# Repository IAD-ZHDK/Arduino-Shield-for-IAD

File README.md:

# Arduino-Shield-for-IAD

A simple prototyping shield with Lynx Smart Servo and qwiic/stema connectors for both Ardiuino UNO and MKR board shapes.  

MKR                                                      |  UNO 
:-------------------------------------------------------:|:--------------------------------------------------------:
 |   

The arduino UNO shield uses the following pins for software serial to the LYNX smart servo connector:

rxPin 8

txPin 9

The MKR shield uses the following pins for hardware serial (SAMD21 devices) the LYNX smart servo connector: 

rxPin 1

txPin 0

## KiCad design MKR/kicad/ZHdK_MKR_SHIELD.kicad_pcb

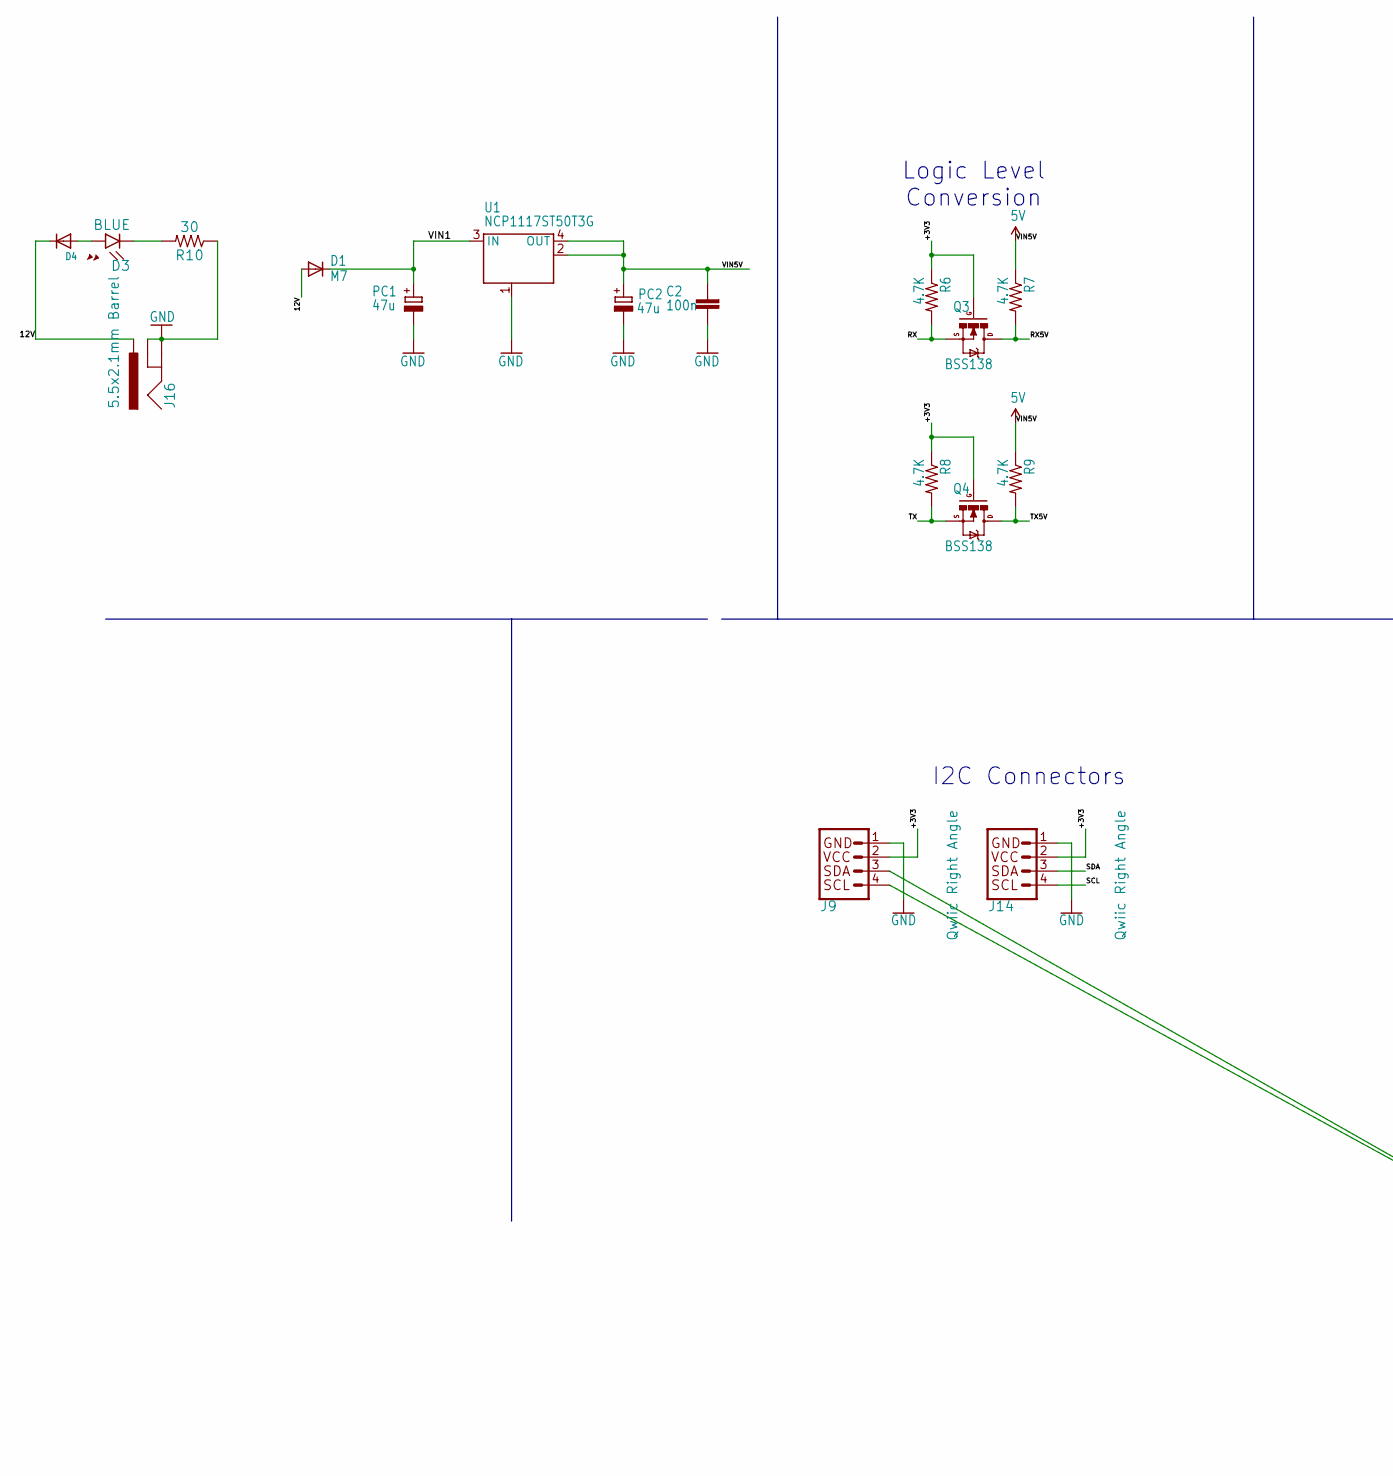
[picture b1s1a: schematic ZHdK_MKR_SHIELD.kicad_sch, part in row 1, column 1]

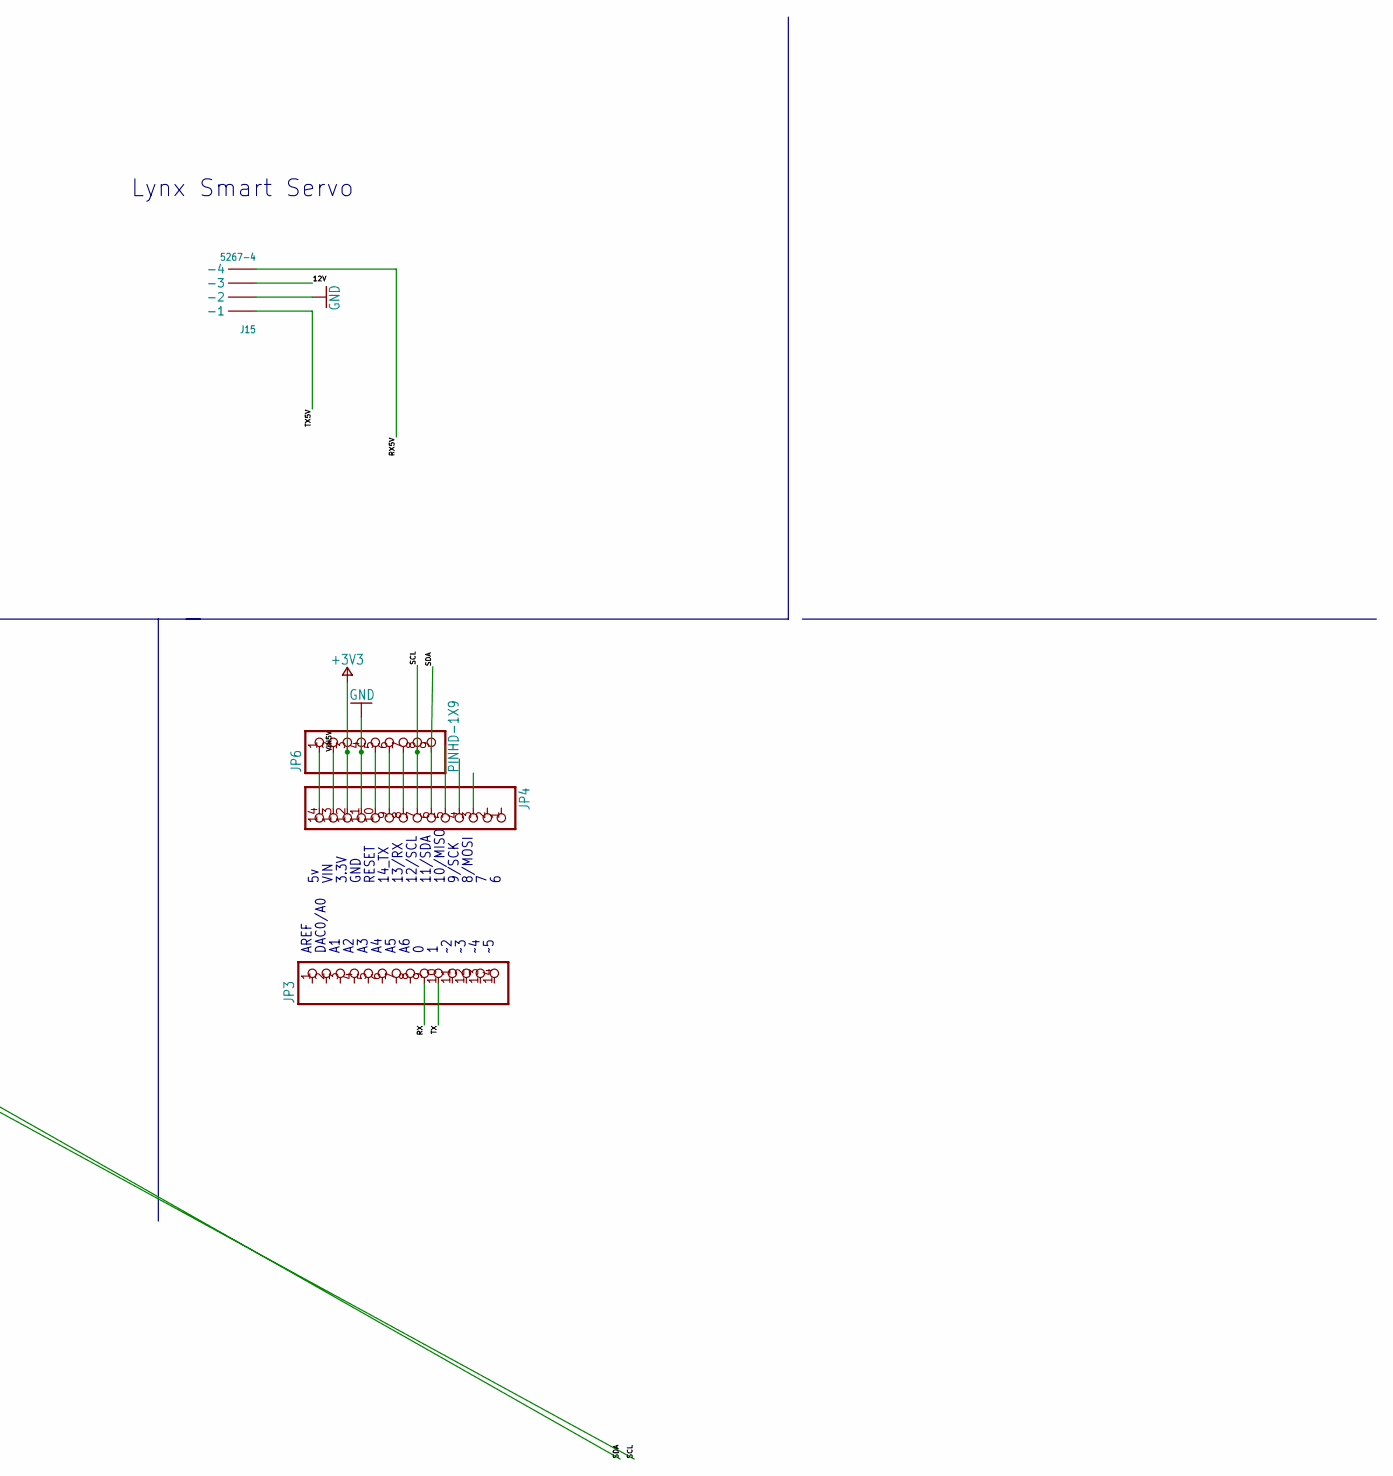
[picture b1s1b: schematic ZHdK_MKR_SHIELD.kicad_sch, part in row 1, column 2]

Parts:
C2: 100n; C0603-ROUND
D1: M7; SMB
D3: BLUE; LED-0603
D4: 9V; SOD-123
J9, J14: Qwiic Right Angle; 1X04_1MM_RA
J15: 5267-4
J16: 5.5x2.1mm Barrel; POWER_JACK_SMD
JP3, JP4: -; 1X14
JP6: PINHD-1X9; 1X09
PC1, PC2: 47u; PANASONIC_D
Q3, Q4: BSS138; SOT23-3
R6, R7, R8, R9: 4.7K; 0603-RES
R10: 30; 0603
U1: NCP1117ST50T3G; SOT223

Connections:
12V: D1.A, D4.C, J15.P$3 (-3), J16.VIN0 (PWR)
+3V3: J9.2, J14.2, JP4.12, JP6.3, Q3.1 (G), Q4.1 (G), R6.1, R8.1
GND: C2.1, J9.1, J14.1, J15.P$2 (-2), J16.GND (GNDBREAK), J16.P$4 (GND), JP4.11, JP6.4, PC1.-, PC2.-, R10.1, U1.1 (GND/ADJ)
unnamed: JP4.14, JP6.1
unnamed: JP4.10, JP6.5
unnamed: JP4.9, JP6.6
unnamed: JP4.8, JP6.7
unnamed: D3.A, D4.A
unnamed: D3.C, R10.2
RX: JP3.9, Q3.2 (S), R6.2
RX5V: J15.P$4 (-4), Q3.3 (D), R7.2
SCL: J9.4, J14.4, JP4.7, JP6.8
SDA: J9.3, J14.3, JP4.6, JP6.9
TX: JP3.10, Q4.2 (S), R8.2
TX5V: J15.P$1 (-1), Q4.3 (D), R9.2
VIN1: D1.C, PC1.+, U1.3 (IN)
VIN5V: C2.2, JP4.13, JP6.2, PC2.+, R7.1, R9.1, U1.2 (OUT@1), U1.4 (OUT)

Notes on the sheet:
GND
3.3V
I2C Connectors
8/MOSI
AREF
11/SDA
9/SCK
13/RX
10/MISO
RESET
Lynx Smart Servo
14_TX
DAC0/A0
12/SCL
Logic Level Conversion
VIN

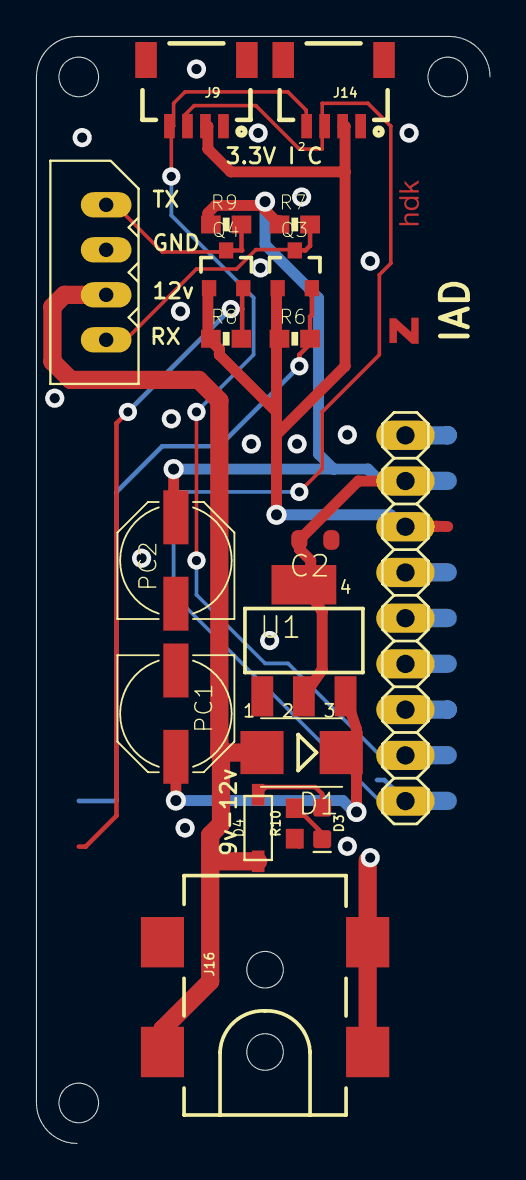
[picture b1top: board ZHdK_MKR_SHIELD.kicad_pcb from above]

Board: 2 copper layers, 25.2 x 61.5 mm, 23 parts (0 on the bottom side), 13 nets.

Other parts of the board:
U$2: ZHDK_LOGO
UNK_HOLE_0: dummyfp0
UNK_HOLE_2: dummyfp2
UNK_HOLE_3: dummyfp3

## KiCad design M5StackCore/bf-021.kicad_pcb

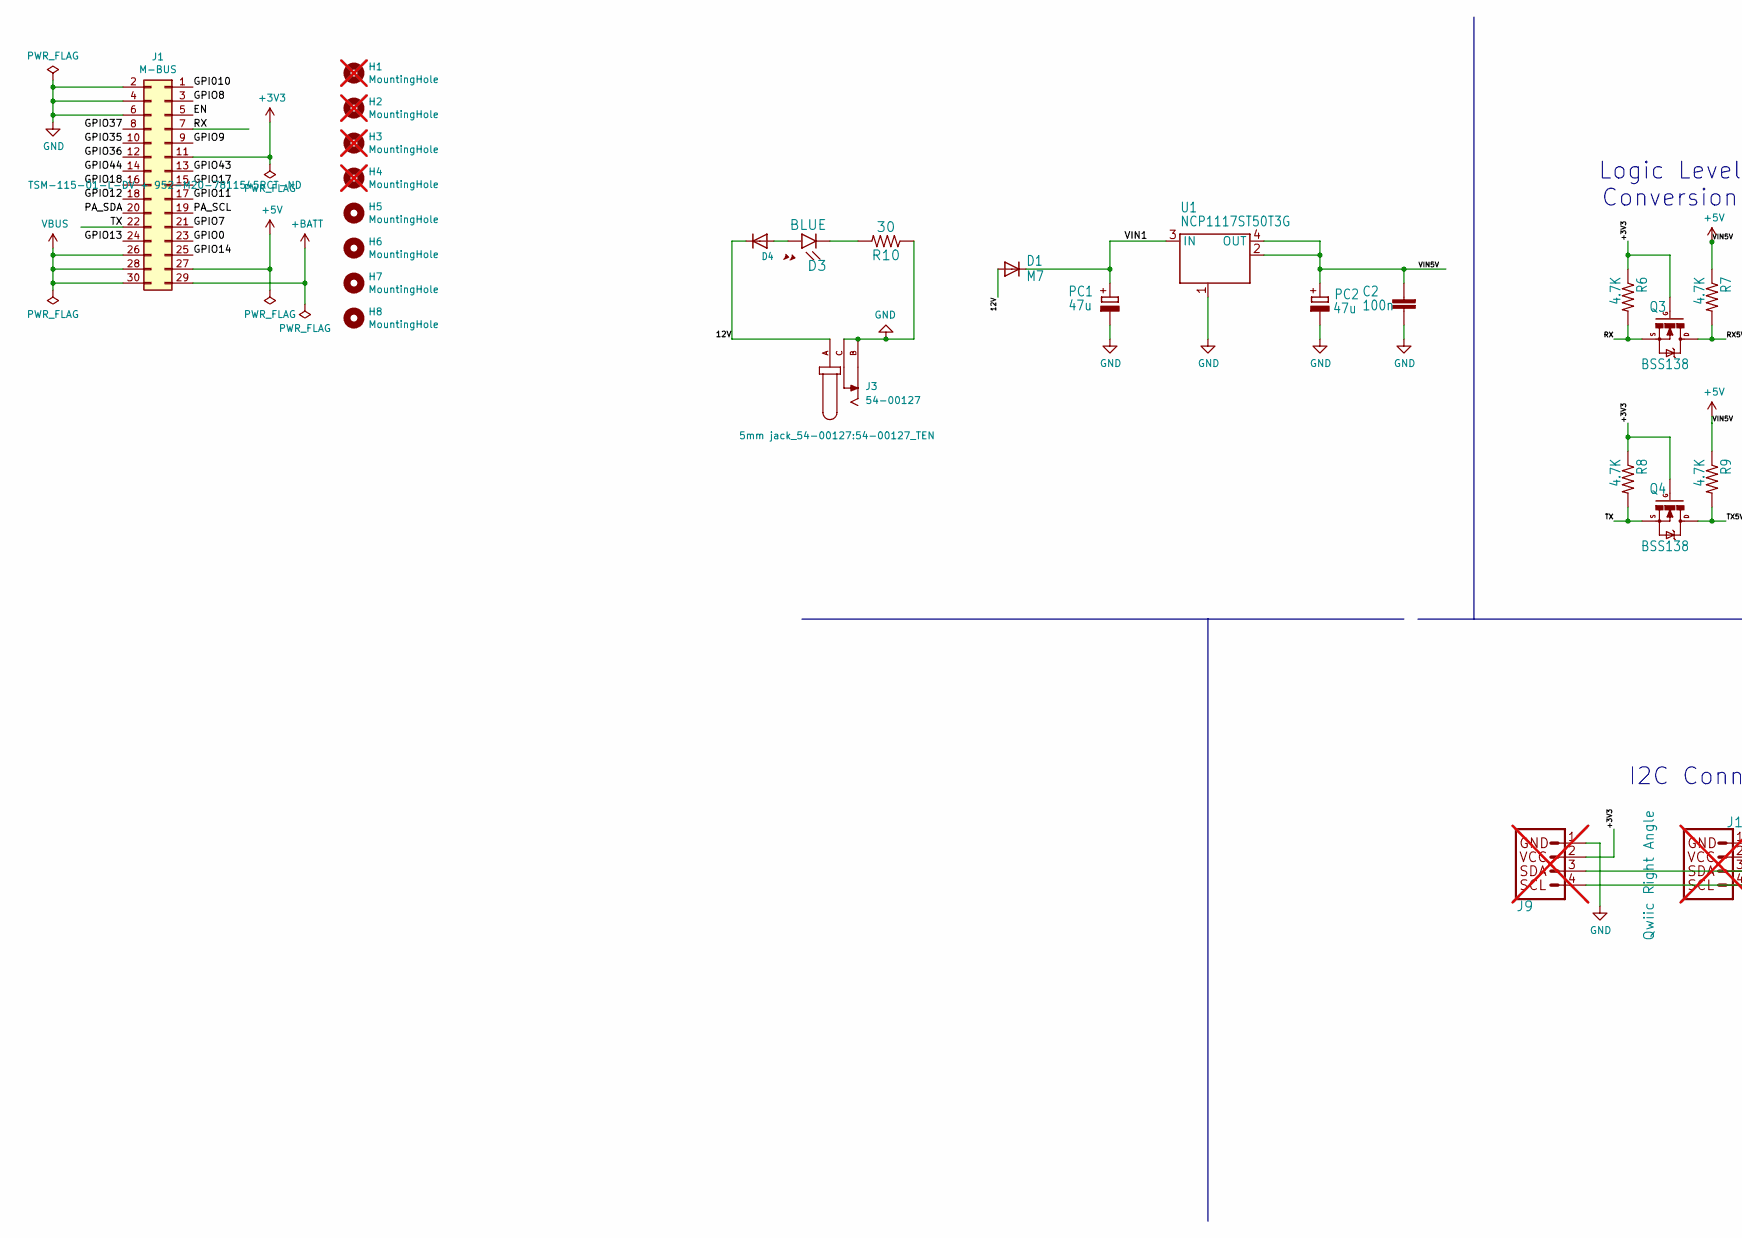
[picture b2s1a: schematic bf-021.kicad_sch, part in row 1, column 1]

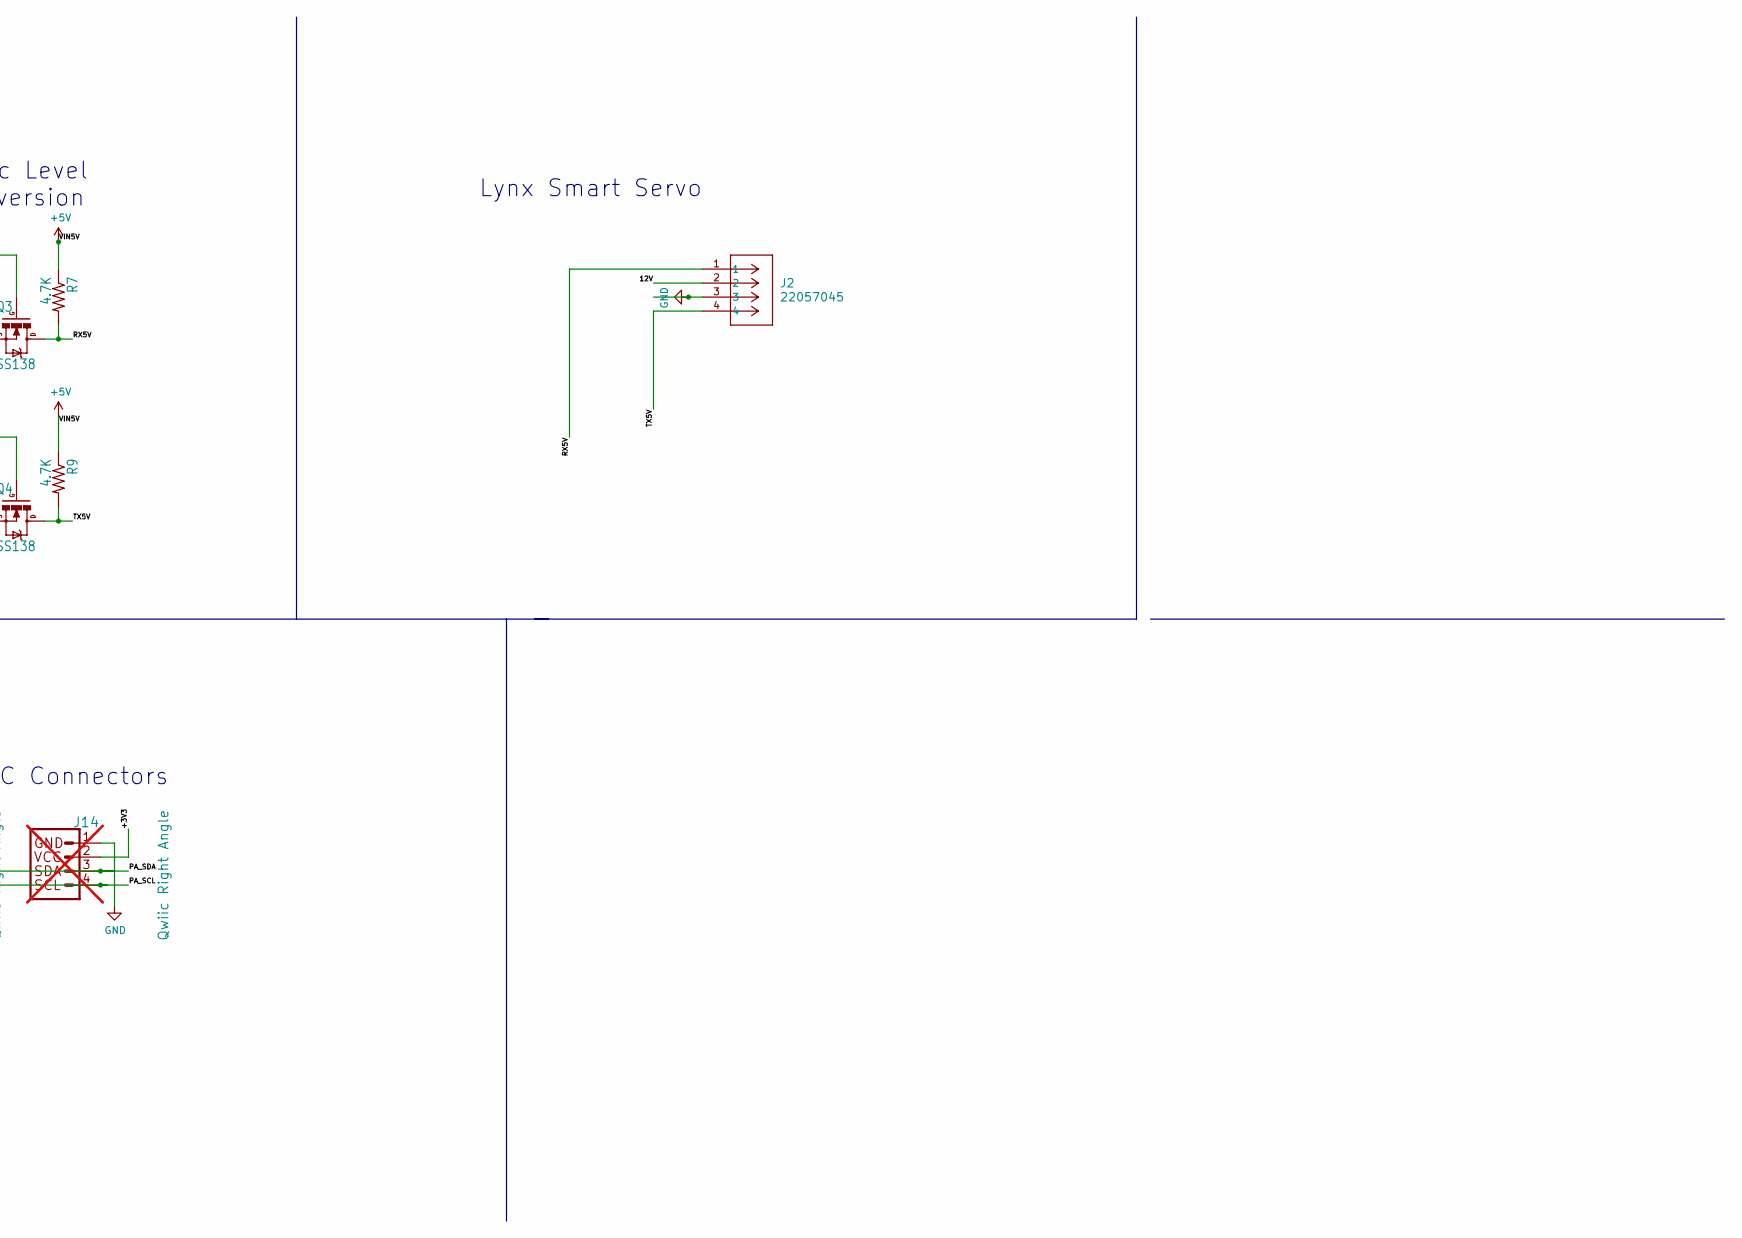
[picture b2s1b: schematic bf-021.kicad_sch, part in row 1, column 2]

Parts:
C2: 100n; C0603-ROUND
D1: M7; SMB
D3: BLUE; LED-0603
D4: 9V; SOD-123
H1, H2, H3, H4: MountingHole; BF@MountingHole_3.2mm_M3; not fitted
H5, H6, H7, H8: MountingHole; BF@MountingHole_2.2mm_M2
J1: M-BUS; BF@M5Stack_MBUS
J2: 22057045; CONN_22057045_MOL
J3: 54-00127; 54-00127_TEN; PARTREV A
J9, J14: Qwiic Right Angle; 1X04_1MM_RA; not fitted
PC1, PC2: 47u; PANASONIC_D
Q3, Q4: BSS138; SOT23-3
R6, R7, R8, R9: 4.7K; 0603-RES
R10: 30; 0603
U1: NCP1117ST50T3G; SOT223

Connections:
+3V3: J1.11, J9.2, J14.2, Q3.1 (G), Q4.1 (G), R6.1, R8.1
+5V: C2.2, J1.27, PC2.+, R7.1, R9.1, U1.2 (OUT@1), U1.4 (OUT)
+BATT: J1.29
/12V: D1.A, D4.C, J2.2, J3.A
/EN: J1.5
/GPI010: J1.1
/GPIO0: J1.23
/GPIO5: J1.9
/GPIO7: J1.21
/GPIO8: J1.3
/GPIO11: J1.17
/GPIO12: J1.18
/GPIO13: J1.24
/GPIO14: J1.25
/GPIO17: J1.15
/GPIO18: J1.16
/GPIO35: J1.10
/GPIO36: J1.12
/GPIO37: J1.8
/GPIO43: J1.13
/GPIO44: J1.14
/PA_SCL: J1.19, J9.4, J14.4
/PA_SDA: J1.20, J9.3, J14.3
/RX: J1.7, Q3.2 (S), R6.2
/RX5V: J2.1, Q3.3 (D), R7.2
/TX: J1.22, Q4.2 (S), R8.2
/TX5V: J2.4, Q4.3 (D), R9.2
/VIN1: D1.C, PC1.+, U1.3 (IN)
GND: C2.1, J1.2, J1.4, J1.6, J2.3, J3.B, J3.C, J9.1, J14.1, PC1.-, PC2.-, R10.1, U1.1 (GND/ADJ)
unnamed: D3.A, D4.A
unnamed: D3.C, R10.2
VBUS: J1.26, J1.28, J1.30

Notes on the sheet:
I2C Connectors
Lynx Smart Servo
Logic Level Conversion

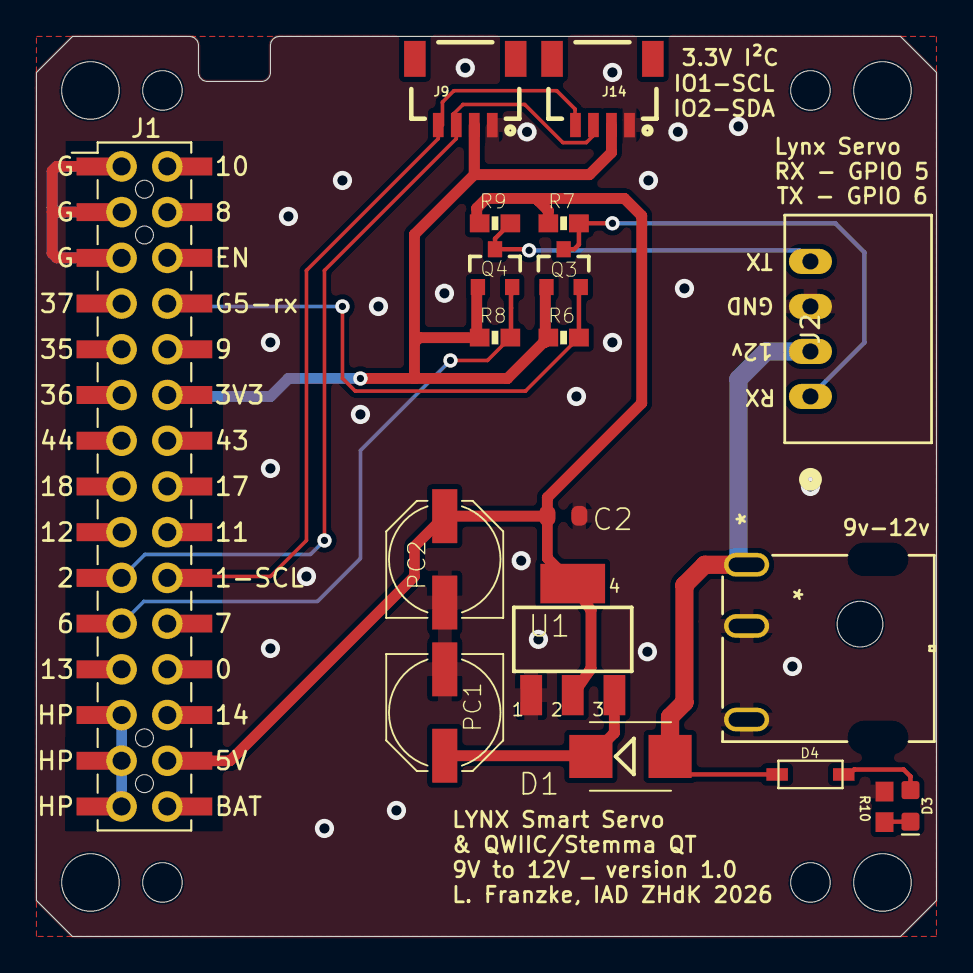
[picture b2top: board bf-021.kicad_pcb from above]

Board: 2 copper layers, 50.0 x 50.0 mm, 27 parts (0 on the bottom side), 14 nets.

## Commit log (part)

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2021-10-06 Init commit
2021-10-06 fix resistor value
2023-05-03 added MKR version
2023-05-03 added arduino examples

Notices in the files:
M5StackCore/bf-021.kicad_pcb:
Copyright 2022 BotanicFields, Inc.
